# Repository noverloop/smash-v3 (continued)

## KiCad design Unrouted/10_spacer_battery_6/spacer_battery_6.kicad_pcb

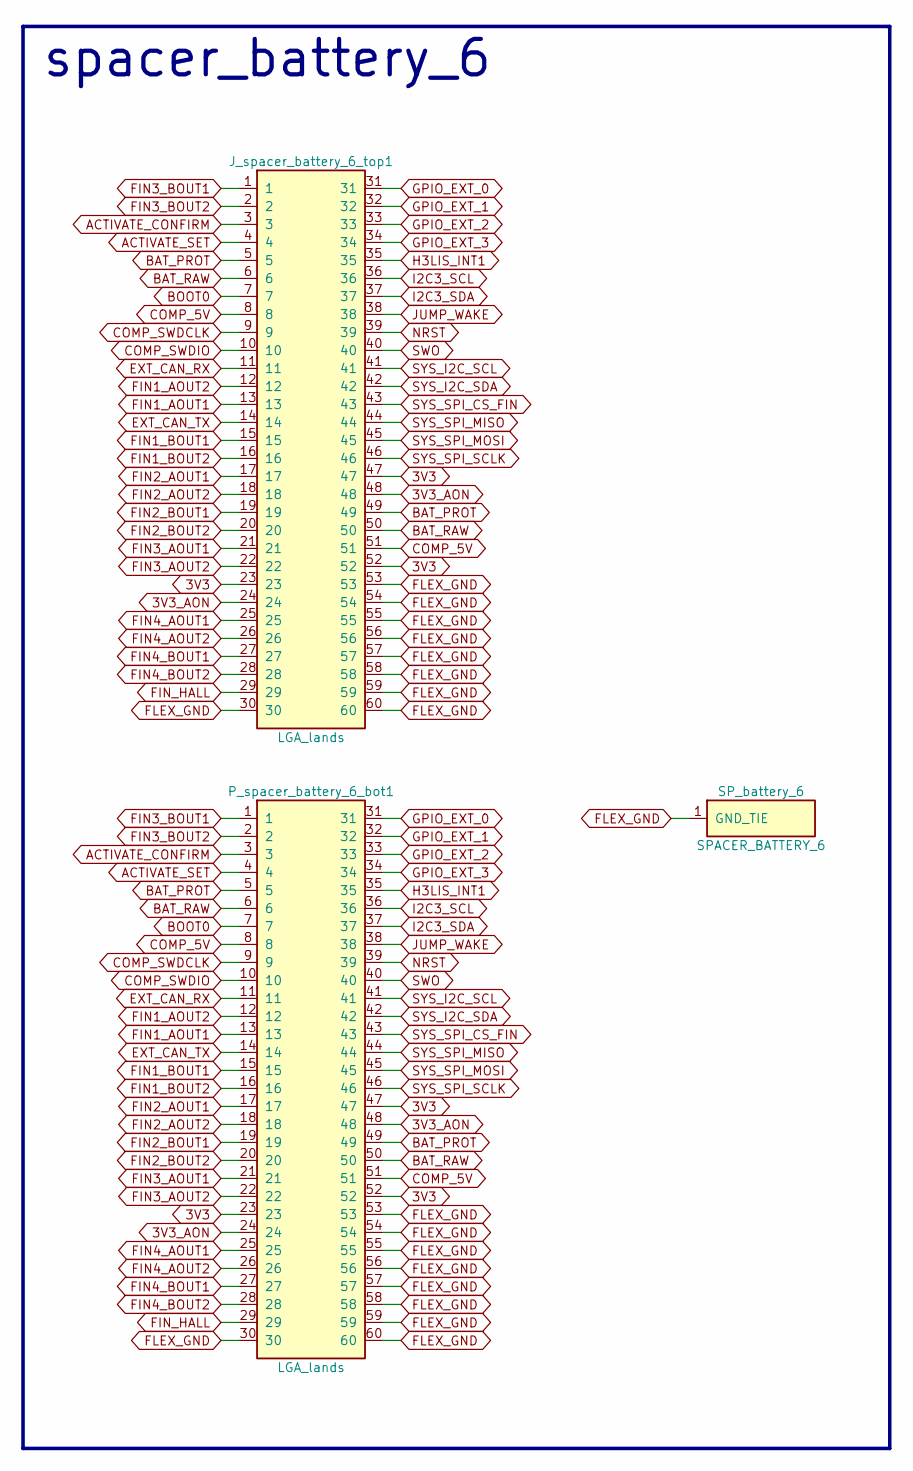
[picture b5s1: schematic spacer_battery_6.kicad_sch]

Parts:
J_spacer_battery_6_top1: LGA_lands; J_spacer_battery_6_top; MPN LGA_lands
P_spacer_battery_6_bot1: LGA_lands; P_spacer_battery_6_bot; MPN LGA_lands
SP_battery_6: SPACER_BATTERY_6; Spacer_Mechanical_34mm

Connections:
3V3: J_spacer_battery_6_top1.23, J_spacer_battery_6_top1.47, J_spacer_battery_6_top1.52, P_spacer_battery_6_bot1.23, P_spacer_battery_6_bot1.47, P_spacer_battery_6_bot1.52
3V3_AON: J_spacer_battery_6_top1.24, J_spacer_battery_6_top1.48, P_spacer_battery_6_bot1.24, P_spacer_battery_6_bot1.48
ACTIVATE_CONFIRM: J_spacer_battery_6_top1.3, P_spacer_battery_6_bot1.3
ACTIVATE_SET: J_spacer_battery_6_top1.4, P_spacer_battery_6_bot1.4
BAT_PROT: J_spacer_battery_6_top1.5, J_spacer_battery_6_top1.49, P_spacer_battery_6_bot1.5, P_spacer_battery_6_bot1.49
BAT_RAW: J_spacer_battery_6_top1.6, J_spacer_battery_6_top1.50, P_spacer_battery_6_bot1.6, P_spacer_battery_6_bot1.50
BOOT0: J_spacer_battery_6_top1.7, P_spacer_battery_6_bot1.7
COMP_5V: J_spacer_battery_6_top1.8, J_spacer_battery_6_top1.51, P_spacer_battery_6_bot1.8, P_spacer_battery_6_bot1.51
COMP_SWDCLK: J_spacer_battery_6_top1.9, P_spacer_battery_6_bot1.9
COMP_SWDIO: J_spacer_battery_6_top1.10, P_spacer_battery_6_bot1.10
EXT_CAN_RX: J_spacer_battery_6_top1.11, P_spacer_battery_6_bot1.11
EXT_CAN_TX: J_spacer_battery_6_top1.14, P_spacer_battery_6_bot1.14
FIN1_AOUT1: J_spacer_battery_6_top1.13, P_spacer_battery_6_bot1.13
FIN1_AOUT2: J_spacer_battery_6_top1.12, P_spacer_battery_6_bot1.12
FIN1_BOUT1: J_spacer_battery_6_top1.15, P_spacer_battery_6_bot1.15
FIN1_BOUT2: J_spacer_battery_6_top1.16, P_spacer_battery_6_bot1.16
FIN2_AOUT1: J_spacer_battery_6_top1.17, P_spacer_battery_6_bot1.17
FIN2_AOUT2: J_spacer_battery_6_top1.18, P_spacer_battery_6_bot1.18
FIN2_BOUT1: J_spacer_battery_6_top1.19, P_spacer_battery_6_bot1.19
FIN2_BOUT2: J_spacer_battery_6_top1.20, P_spacer_battery_6_bot1.20
FIN3_AOUT1: J_spacer_battery_6_top1.21, P_spacer_battery_6_bot1.21
FIN3_AOUT2: J_spacer_battery_6_top1.22, P_spacer_battery_6_bot1.22
FIN3_BOUT1: J_spacer_battery_6_top1.1, P_spacer_battery_6_bot1.1
FIN3_BOUT2: J_spacer_battery_6_top1.2, P_spacer_battery_6_bot1.2
FIN4_AOUT1: J_spacer_battery_6_top1.25, P_spacer_battery_6_bot1.25
FIN4_AOUT2: J_spacer_battery_6_top1.26, P_spacer_battery_6_bot1.26
FIN4_BOUT1: J_spacer_battery_6_top1.27, P_spacer_battery_6_bot1.27
FIN4_BOUT2: J_spacer_battery_6_top1.28, P_spacer_battery_6_bot1.28
FIN_HALL: J_spacer_battery_6_top1.29, P_spacer_battery_6_bot1.29
FLEX_GND: J_spacer_battery_6_top1.30, J_spacer_battery_6_top1.53, J_spacer_battery_6_top1.54, J_spacer_battery_6_top1.55, J_spacer_battery_6_top1.56, J_spacer_battery_6_top1.57, J_spacer_battery_6_top1.58, J_spacer_battery_6_top1.59, J_spacer_battery_6_top1.60, P_spacer_battery_6_bot1.30, P_spacer_battery_6_bot1.53, P_spacer_battery_6_bot1.54, P_spacer_battery_6_bot1.55, P_spacer_battery_6_bot1.56, P_spacer_battery_6_bot1.57, P_spacer_battery_6_bot1.58, P_spacer_battery_6_bot1.59, P_spacer_battery_6_bot1.60, SP_battery_6.1
GPIO_EXT_0: J_spacer_battery_6_top1.31, P_spacer_battery_6_bot1.31
GPIO_EXT_1: J_spacer_battery_6_top1.32, P_spacer_battery_6_bot1.32
GPIO_EXT_2: J_spacer_battery_6_top1.33, P_spacer_battery_6_bot1.33
GPIO_EXT_3: J_spacer_battery_6_top1.34, P_spacer_battery_6_bot1.34
H3LIS_INT1: J_spacer_battery_6_top1.35, P_spacer_battery_6_bot1.35
I2C3_SCL: J_spacer_battery_6_top1.36, P_spacer_battery_6_bot1.36
I2C3_SDA: J_spacer_battery_6_top1.37, P_spacer_battery_6_bot1.37
JUMP_WAKE: J_spacer_battery_6_top1.38, P_spacer_battery_6_bot1.38
NRST: J_spacer_battery_6_top1.39, P_spacer_battery_6_bot1.39
SWO: J_spacer_battery_6_top1.40, P_spacer_battery_6_bot1.40
SYS_I2C_SCL: J_spacer_battery_6_top1.41, P_spacer_battery_6_bot1.41
SYS_I2C_SDA: J_spacer_battery_6_top1.42, P_spacer_battery_6_bot1.42
SYS_SPI_CS_FIN: J_spacer_battery_6_top1.43, P_spacer_battery_6_bot1.43
SYS_SPI_MISO: J_spacer_battery_6_top1.44, P_spacer_battery_6_bot1.44
SYS_SPI_MOSI: J_spacer_battery_6_top1.45, P_spacer_battery_6_bot1.45
SYS_SPI_SCLK: J_spacer_battery_6_top1.46, P_spacer_battery_6_bot1.46

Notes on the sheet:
spacer_battery_6

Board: 2 copper layers, 4 parts (1 on the bottom side), 46 nets, no tracks yet.

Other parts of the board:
MH1: smash_mech_potting

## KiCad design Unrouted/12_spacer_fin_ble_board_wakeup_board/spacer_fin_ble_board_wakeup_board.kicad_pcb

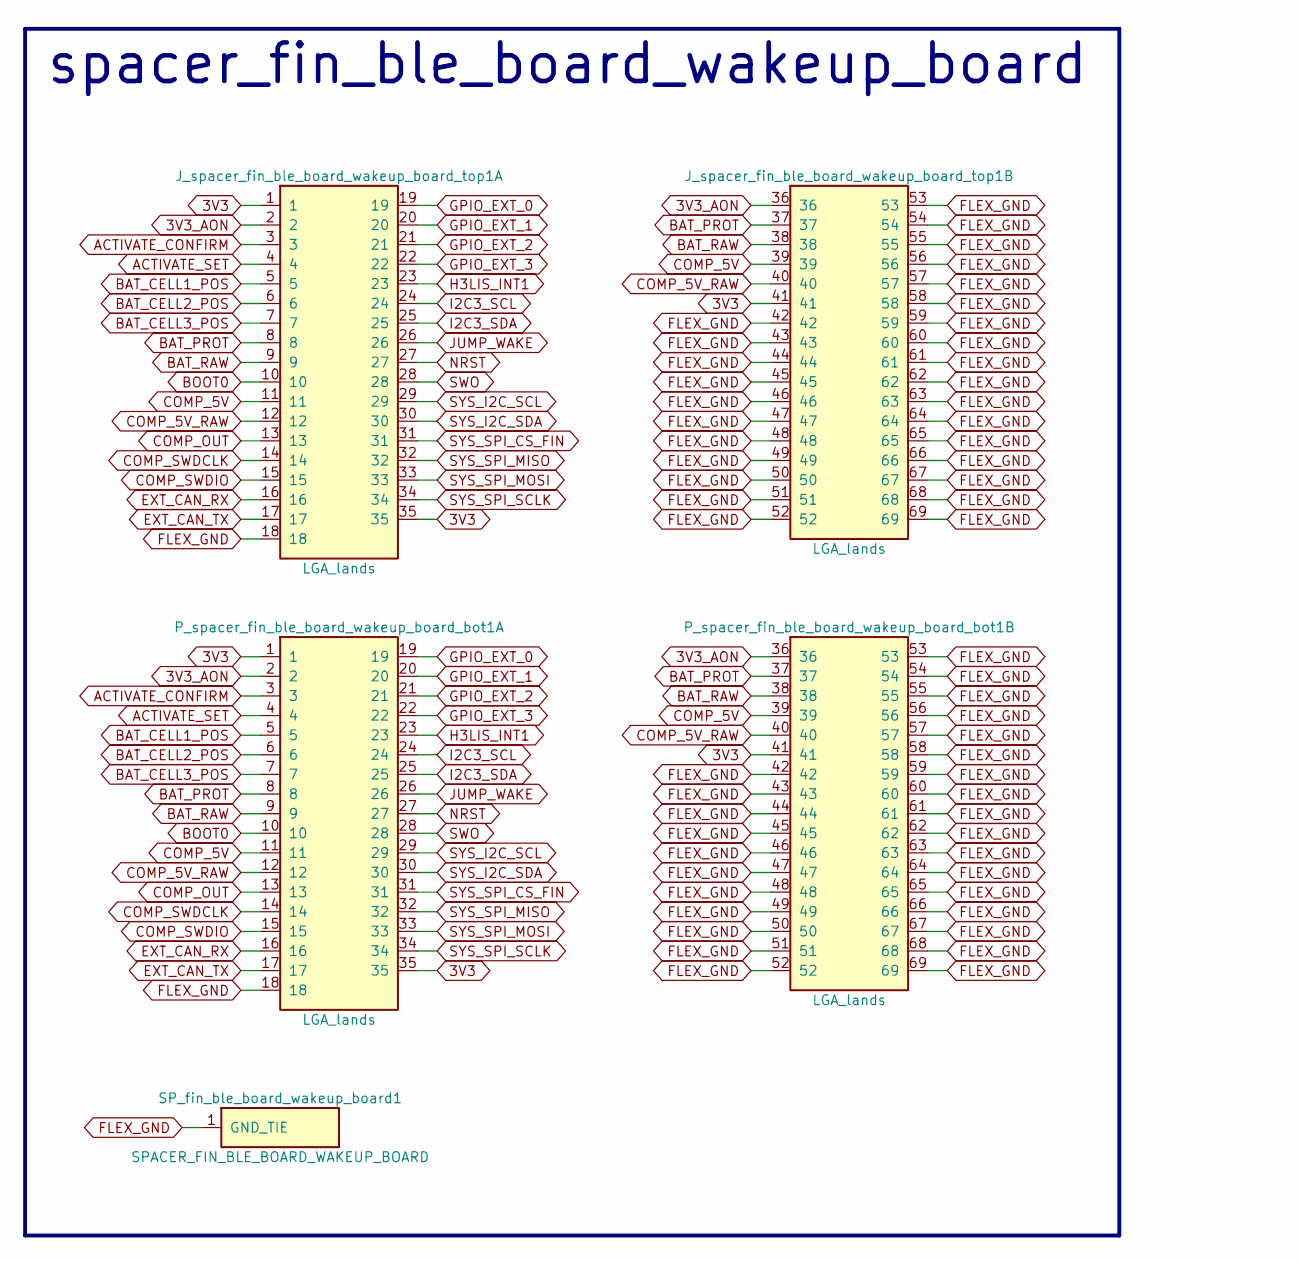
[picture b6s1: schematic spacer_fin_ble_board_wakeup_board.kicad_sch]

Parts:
J_spacer_fin_ble_board_wakeup_board_top1: LGA_lands; J_spacer_fin_ble_board_wakeup_board_top; MPN LGA_lands
P_spacer_fin_ble_board_wakeup_board_bot1: LGA_lands; P_spacer_fin_ble_board_wakeup_board_bot; MPN LGA_lands
SP_fin_ble_board_wakeup_board1: SPACER_FIN_BLE_BOARD_WAKEUP_BOARD; Spacer_Mechanical_34mm

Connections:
3V3: J_spacer_fin_ble_board_wakeup_board_top1.1, J_spacer_fin_ble_board_wakeup_board_top1.35, J_spacer_fin_ble_board_wakeup_board_top1.41, P_spacer_fin_ble_board_wakeup_board_bot1.1, P_spacer_fin_ble_board_wakeup_board_bot1.35, P_spacer_fin_ble_board_wakeup_board_bot1.41
3V3_AON: J_spacer_fin_ble_board_wakeup_board_top1.2, J_spacer_fin_ble_board_wakeup_board_top1.36, P_spacer_fin_ble_board_wakeup_board_bot1.2, P_spacer_fin_ble_board_wakeup_board_bot1.36
ACTIVATE_CONFIRM: J_spacer_fin_ble_board_wakeup_board_top1.3, P_spacer_fin_ble_board_wakeup_board_bot1.3
ACTIVATE_SET: J_spacer_fin_ble_board_wakeup_board_top1.4, P_spacer_fin_ble_board_wakeup_board_bot1.4
BAT_CELL1_POS: J_spacer_fin_ble_board_wakeup_board_top1.5, P_spacer_fin_ble_board_wakeup_board_bot1.5
BAT_CELL2_POS: J_spacer_fin_ble_board_wakeup_board_top1.6, P_spacer_fin_ble_board_wakeup_board_bot1.6
BAT_CELL3_POS: J_spacer_fin_ble_board_wakeup_board_top1.7, P_spacer_fin_ble_board_wakeup_board_bot1.7
BAT_PROT: J_spacer_fin_ble_board_wakeup_board_top1.8, J_spacer_fin_ble_board_wakeup_board_top1.37, P_spacer_fin_ble_board_wakeup_board_bot1.8, P_spacer_fin_ble_board_wakeup_board_bot1.37
BAT_RAW: J_spacer_fin_ble_board_wakeup_board_top1.9, J_spacer_fin_ble_board_wakeup_board_top1.38, P_spacer_fin_ble_board_wakeup_board_bot1.9, P_spacer_fin_ble_board_wakeup_board_bot1.38
BOOT0: J_spacer_fin_ble_board_wakeup_board_top1.10, P_spacer_fin_ble_board_wakeup_board_bot1.10
COMP_5V: J_spacer_fin_ble_board_wakeup_board_top1.11, J_spacer_fin_ble_board_wakeup_board_top1.39, P_spacer_fin_ble_board_wakeup_board_bot1.11, P_spacer_fin_ble_board_wakeup_board_bot1.39
COMP_5V_RAW: J_spacer_fin_ble_board_wakeup_board_top1.12, J_spacer_fin_ble_board_wakeup_board_top1.40, P_spacer_fin_ble_board_wakeup_board_bot1.12, P_spacer_fin_ble_board_wakeup_board_bot1.40
COMP_OUT: J_spacer_fin_ble_board_wakeup_board_top1.13, P_spacer_fin_ble_board_wakeup_board_bot1.13
COMP_SWDCLK: J_spacer_fin_ble_board_wakeup_board_top1.14, P_spacer_fin_ble_board_wakeup_board_bot1.14
COMP_SWDIO: J_spacer_fin_ble_board_wakeup_board_top1.15, P_spacer_fin_ble_board_wakeup_board_bot1.15
EXT_CAN_RX: J_spacer_fin_ble_board_wakeup_board_top1.16, P_spacer_fin_ble_board_wakeup_board_bot1.16
EXT_CAN_TX: J_spacer_fin_ble_board_wakeup_board_top1.17, P_spacer_fin_ble_board_wakeup_board_bot1.17
FLEX_GND: J_spacer_fin_ble_board_wakeup_board_top1.18, J_spacer_fin_ble_board_wakeup_board_top1.42, J_spacer_fin_ble_board_wakeup_board_top1.43, J_spacer_fin_ble_board_wakeup_board_top1.44, J_spacer_fin_ble_board_wakeup_board_top1.45, J_spacer_fin_ble_board_wakeup_board_top1.46, J_spacer_fin_ble_board_wakeup_board_top1.47, J_spacer_fin_ble_board_wakeup_board_top1.48, J_spacer_fin_ble_board_wakeup_board_top1.49, J_spacer_fin_ble_board_wakeup_board_top1.50, J_spacer_fin_ble_board_wakeup_board_top1.51, J_spacer_fin_ble_board_wakeup_board_top1.52, J_spacer_fin_ble_board_wakeup_board_top1.53, J_spacer_fin_ble_board_wakeup_board_top1.54, J_spacer_fin_ble_board_wakeup_board_top1.55, J_spacer_fin_ble_board_wakeup_board_top1.56, J_spacer_fin_ble_board_wakeup_board_top1.57, J_spacer_fin_ble_board_wakeup_board_top1.58, J_spacer_fin_ble_board_wakeup_board_top1.59, J_spacer_fin_ble_board_wakeup_board_top1.60, J_spacer_fin_ble_board_wakeup_board_top1.61, J_spacer_fin_ble_board_wakeup_board_top1.62, J_spacer_fin_ble_board_wakeup_board_top1.63, J_spacer_fin_ble_board_wakeup_board_top1.64, J_spacer_fin_ble_board_wakeup_board_top1.65, J_spacer_fin_ble_board_wakeup_board_top1.66, J_spacer_fin_ble_board_wakeup_board_top1.67, J_spacer_fin_ble_board_wakeup_board_top1.68, J_spacer_fin_ble_board_wakeup_board_top1.69, P_spacer_fin_ble_board_wakeup_board_bot1.18, P_spacer_fin_ble_board_wakeup_board_bot1.42, P_spacer_fin_ble_board_wakeup_board_bot1.43, P_spacer_fin_ble_board_wakeup_board_bot1.44, P_spacer_fin_ble_board_wakeup_board_bot1.45, P_spacer_fin_ble_board_wakeup_board_bot1.46, P_spacer_fin_ble_board_wakeup_board_bot1.47, P_spacer_fin_ble_board_wakeup_board_bot1.48, P_spacer_fin_ble_board_wakeup_board_bot1.49, P_spacer_fin_ble_board_wakeup_board_bot1.50, P_spacer_fin_ble_board_wakeup_board_bot1.51, P_spacer_fin_ble_board_wakeup_board_bot1.52, P_spacer_fin_ble_board_wakeup_board_bot1.53, P_spacer_fin_ble_board_wakeup_board_bot1.54, P_spacer_fin_ble_board_wakeup_board_bot1.55, P_spacer_fin_ble_board_wakeup_board_bot1.56, P_spacer_fin_ble_board_wakeup_board_bot1.57, P_spacer_fin_ble_board_wakeup_board_bot1.58, P_spacer_fin_ble_board_wakeup_board_bot1.59, P_spacer_fin_ble_board_wakeup_board_bot1.60, P_spacer_fin_ble_board_wakeup_board_bot1.61, P_spacer_fin_ble_board_wakeup_board_bot1.62, P_spacer_fin_ble_board_wakeup_board_bot1.63, P_spacer_fin_ble_board_wakeup_board_bot1.64, P_spacer_fin_ble_board_wakeup_board_bot1.65, P_spacer_fin_ble_board_wakeup_board_bot1.66, P_spacer_fin_ble_board_wakeup_board_bot1.67, P_spacer_fin_ble_board_wakeup_board_bot1.68, P_spacer_fin_ble_board_wakeup_board_bot1.69, SP_fin_ble_board_wakeup_board1.1
GPIO_EXT_0: J_spacer_fin_ble_board_wakeup_board_top1.19, P_spacer_fin_ble_board_wakeup_board_bot1.19
GPIO_EXT_1: J_spacer_fin_ble_board_wakeup_board_top1.20, P_spacer_fin_ble_board_wakeup_board_bot1.20
GPIO_EXT_2: J_spacer_fin_ble_board_wakeup_board_top1.21, P_spacer_fin_ble_board_wakeup_board_bot1.21
GPIO_EXT_3: J_spacer_fin_ble_board_wakeup_board_top1.22, P_spacer_fin_ble_board_wakeup_board_bot1.22
H3LIS_INT1: J_spacer_fin_ble_board_wakeup_board_top1.23, P_spacer_fin_ble_board_wakeup_board_bot1.23
I2C3_SCL: J_spacer_fin_ble_board_wakeup_board_top1.24, P_spacer_fin_ble_board_wakeup_board_bot1.24
I2C3_SDA: J_spacer_fin_ble_board_wakeup_board_top1.25, P_spacer_fin_ble_board_wakeup_board_bot1.25
JUMP_WAKE: J_spacer_fin_ble_board_wakeup_board_top1.26, P_spacer_fin_ble_board_wakeup_board_bot1.26
NRST: J_spacer_fin_ble_board_wakeup_board_top1.27, P_spacer_fin_ble_board_wakeup_board_bot1.27
SWO: J_spacer_fin_ble_board_wakeup_board_top1.28, P_spacer_fin_ble_board_wakeup_board_bot1.28
SYS_I2C_SCL: J_spacer_fin_ble_board_wakeup_board_top1.29, P_spacer_fin_ble_board_wakeup_board_bot1.29
SYS_I2C_SDA: J_spacer_fin_ble_board_wakeup_board_top1.30, P_spacer_fin_ble_board_wakeup_board_bot1.30
SYS_SPI_CS_FIN: J_spacer_fin_ble_board_wakeup_board_top1.31, P_spacer_fin_ble_board_wakeup_board_bot1.31
SYS_SPI_MISO: J_spacer_fin_ble_board_wakeup_board_top1.32, P_spacer_fin_ble_board_wakeup_board_bot1.32
SYS_SPI_MOSI: J_spacer_fin_ble_board_wakeup_board_top1.33, P_spacer_fin_ble_board_wakeup_board_bot1.33
SYS_SPI_SCLK: J_spacer_fin_ble_board_wakeup_board_top1.34, P_spacer_fin_ble_board_wakeup_board_bot1.34

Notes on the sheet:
spacer_fin_ble_board_wakeup_board

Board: 2 copper layers, 5 parts (1 on the bottom side), 34 nets, no tracks yet.

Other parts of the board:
MH1, MH2: smash_mech_potting
